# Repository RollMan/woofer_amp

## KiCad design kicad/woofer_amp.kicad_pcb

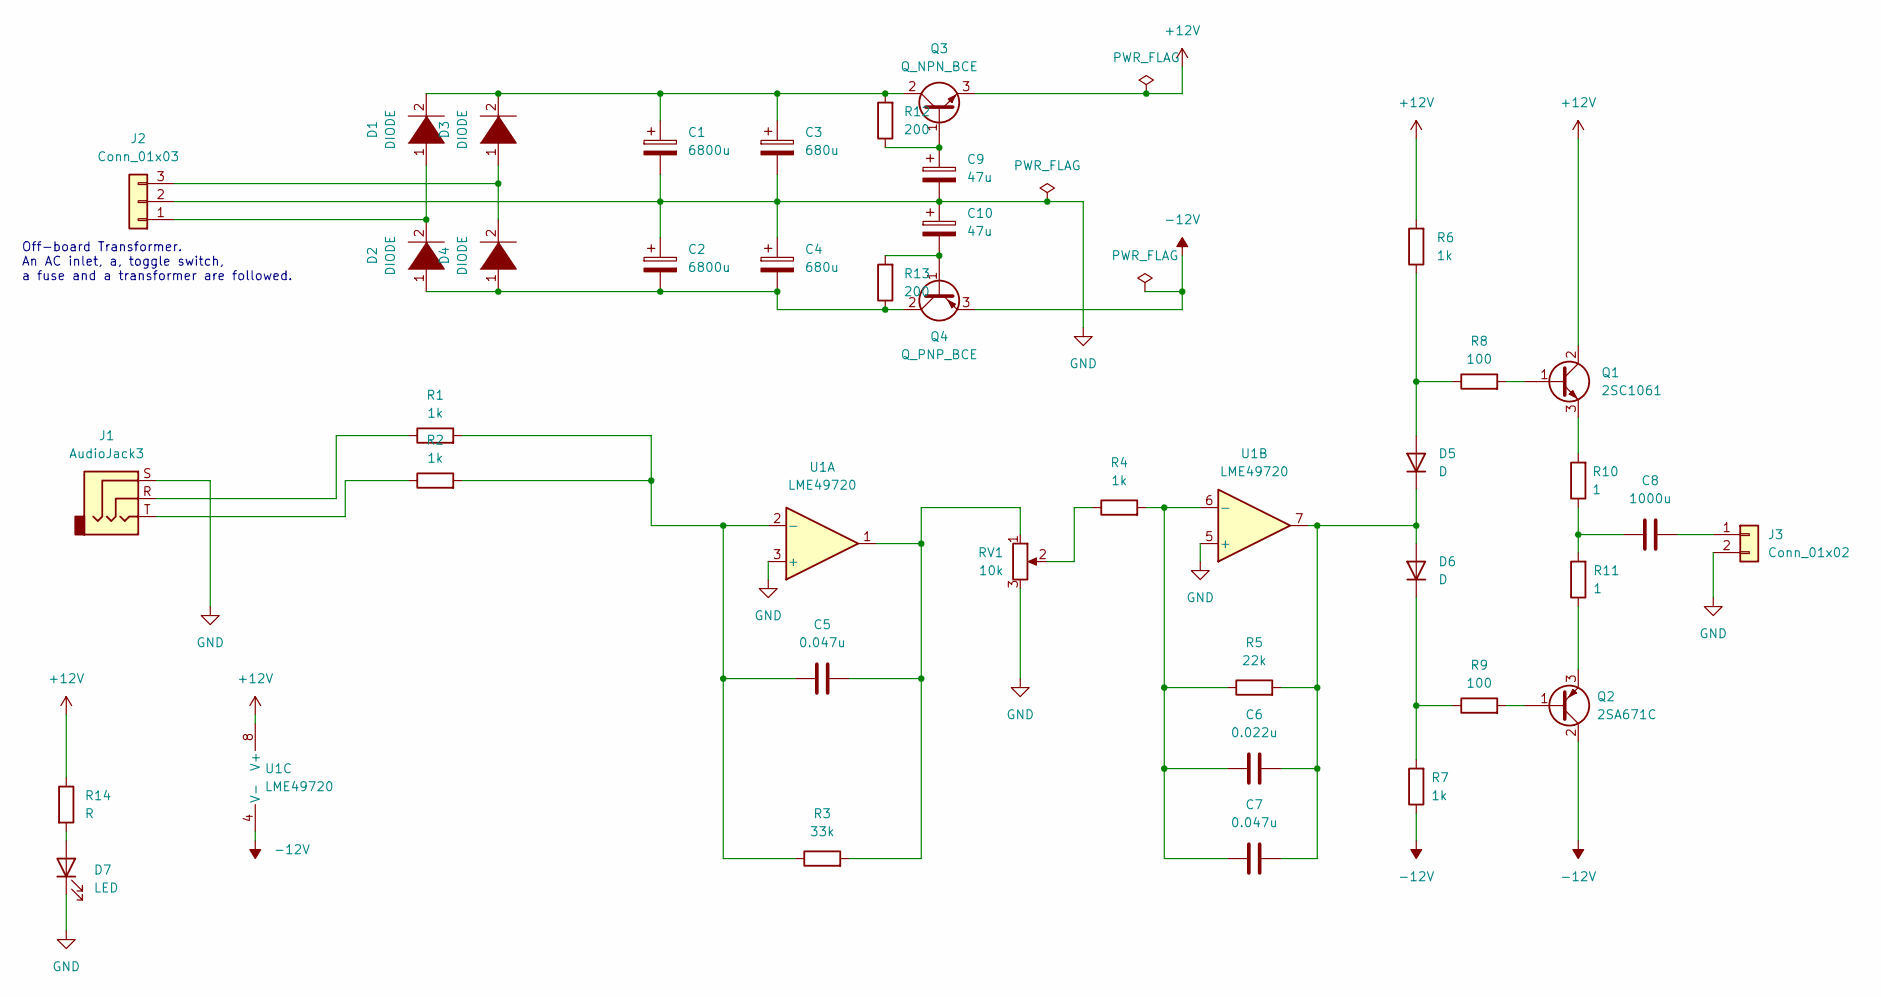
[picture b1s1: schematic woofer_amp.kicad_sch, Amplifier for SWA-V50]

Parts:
C1, C2: 6800u; PinHeader_1x02_P2.54mm_Vertical
C3, C4: 680u; CP_Radial_D8.0mm_P3.80mm
C5, C7: 0.047u; C_Disc_D7.0mm_W2.5mm_P5.00mm
C6: 0.022u; C_Disc_D5.0mm_W2.5mm_P5.00mm
C8: 1000u; C_Radial_D16.0mm_H25.0mm_P7.50mm
C9, C10: 47u; CP_Radial_D8.0mm_P3.80mm
D1, D2, D3, D4: DIODE; D_A-405_P10.16mm_Horizontal
D5, D6: D; D_A-405_P10.16mm_Horizontal
D7: LED; PinHeader_1x02_P2.54mm_Vertical
J1: AudioJack3; PinHeader_1x03_P2.54mm_Vertical
J2: Conn_01x03; PinHeader_1x03_P2.54mm_Vertical
J3: Conn_01x02; PinHeader_1x02_P2.54mm_Vertical
Q1: 2SC1061; TO-220-3_Vertical
Q2: 2SA671C; TO-220-3_Vertical
Q3: Q_NPN_BCE; TO-220-3_Vertical
Q4: Q_PNP_BCE; TO-220-3_Vertical
R1, R2, R4, R6, R7: 1k; R_Axial_DIN0207_L6.3mm_D2.5mm_P10.16mm_Horizontal
R3: 33k; R_Axial_DIN0207_L6.3mm_D2.5mm_P10.16mm_Horizontal
R5: 22k; R_Axial_DIN0207_L6.3mm_D2.5mm_P10.16mm_Horizontal
R8, R9: 100; R_Axial_DIN0207_L6.3mm_D2.5mm_P10.16mm_Horizontal
R10, R11: 1; R_Axial_DIN0207_L6.3mm_D2.5mm_P10.16mm_Horizontal
R12, R13: 200; R_Axial_DIN0207_L6.3mm_D2.5mm_P10.16mm_Horizontal
R14: R; R_Axial_DIN0207_L6.3mm_D2.5mm_P10.16mm_Horizontal
RV1: 10k; PinHeader_1x03_P2.54mm_Vertical
U1: LME49720; DIP-8_W7.62mm

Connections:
+12V: Q1.2 (C), Q3.3 (E), R6.2, R14.1, U1.8 (V+)
-12V: Q2.2 (C), Q4.3 (E), R7.1, U1.4 (V-)
GND: C1.2, C2.1, C3.2, C4.1, C9.2, C10.1, D7.1 (K), J1.S, J2.2, J3.2, RV1.3, U1.3 (+), U1.5 (+)
unnamed: C1.1, C3.1, D1.2 (A), D3.2 (A), Q3.2 (C), R12.2
unnamed: C2.2, C4.2, D2.1 (K), D4.1 (K), Q4.2 (C), R13.1
unnamed: C5.1, R1.2, R2.2, R3.1, U1.2 (-)
unnamed: C5.2, R3.2, RV1.1, U1.1
unnamed: C6.1, C7.1, R4.2, R5.1, U1.6 (-)
unnamed: C6.2, C7.2, D5.1 (K), D6.2 (A), R5.2, U1.7
unnamed: C8.1, R10.1, R11.2
unnamed: C8.2, J3.1
unnamed: C9.1, Q3.1 (B), R12.1
unnamed: C10.2, Q4.1 (B), R13.2
unnamed: D1.1 (K), D2.2 (A), J2.1
unnamed: D3.1 (K), D4.2 (A), J2.3
unnamed: D5.2 (A), R6.1, R8.1
unnamed: D6.1 (K), R7.2, R9.1
unnamed: D7.2 (A), R14.2
unnamed: J1.R, R1.1
unnamed: J1.T, R2.1
unnamed: Q1.1 (B), R8.2
unnamed: Q1.3 (E), R10.2
unnamed: Q2.1 (B), R9.2
unnamed: Q2.3 (E), R11.1
unnamed: R4.1, RV1.2

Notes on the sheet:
Off-board Transformer. An AC inlet, a, toggle switch, a fuse and a transformer are followed.

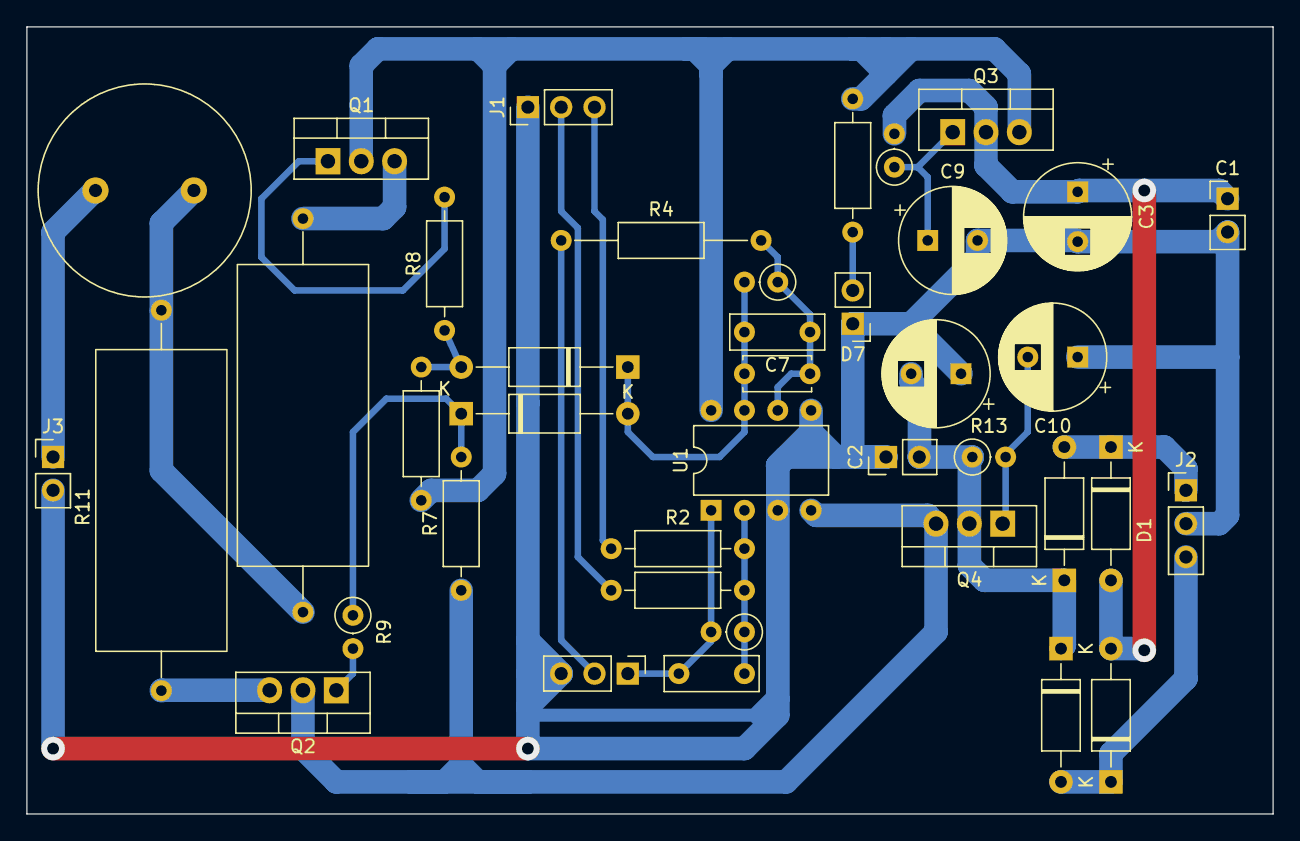
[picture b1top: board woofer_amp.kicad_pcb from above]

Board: 2 copper layers, 95.0 x 60.0 mm, 40 parts (0 on the bottom side), 25 nets.
